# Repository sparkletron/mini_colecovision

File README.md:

# Mini Colecovision Project with Super Game Module Support
### Schematic, PCB, and CPLD design.

---

  author: Jay Convertino

  date: 2024.03.24

  details: A Super Game Module Compatible Colecovision that is much smaller than the original, and only uses +5v.

  license: MIT

---

## LICENSE
  - All files related to or generated from the KiCAD source fall under the MIT license.
  - All files related to or generated from the Verilog source fall under the MIT license.
  - All files generated by me, Jay Convertino, fall under the MIT license.
  - All files from other sources fall under the license of their specification.

## RELEASE VERSIONS
### Current
  - 1.0.1 - Fixed opcode games AY check for super game module.

### Past
  - 1.0.0 - First working version
  - DEV

### MISC
  - std_v1 - A branch that contains the first version with standard colecovision compatibility only.

## Intro
  This is a miniturization of the original colecovision. All logic is simplified to a single CPLD.

## Documentation
  For detailed usage information, please navigate to one of the following sources. They are the same, just in a different format.
  - [mini_colecovision.pdf](docs/manual/mini_colecovision.pdf)
  - [github page](https://sparkletron.github.io/mini_colecovision/)

## SOURCES
### Schematic Check
  - Righteous Tentacle Colecovision : https://github.com/sparkletron/righteous_tentacle_colecovision : Jay Convertino

## SOFTWARE REQUIREMENTS
  - KiCAD v7.X
  - Quartus v13.0.1sp1 web edition
  - Altera USB Blaster

## BUILD TIPS
  This design is made so anyone can build this. Though it will need a board from a PCB manufacture due to the small pitch and
  vias. There are only a few SMD devices, the CPU, a cap, and a few resistors. These are larger to help make soldering easier.

  Recommend populating the SMD parts first, then moving on to the through hole parts from passive to active. If you do not plan
  on using a battery pack the shotkey diodes can be omitted.

  This is a 4 layer board, power and ground planes are run on the two internal planes.

  All case parts are ABS Plastic.

## Completed Project Image

## PCB IMAGE

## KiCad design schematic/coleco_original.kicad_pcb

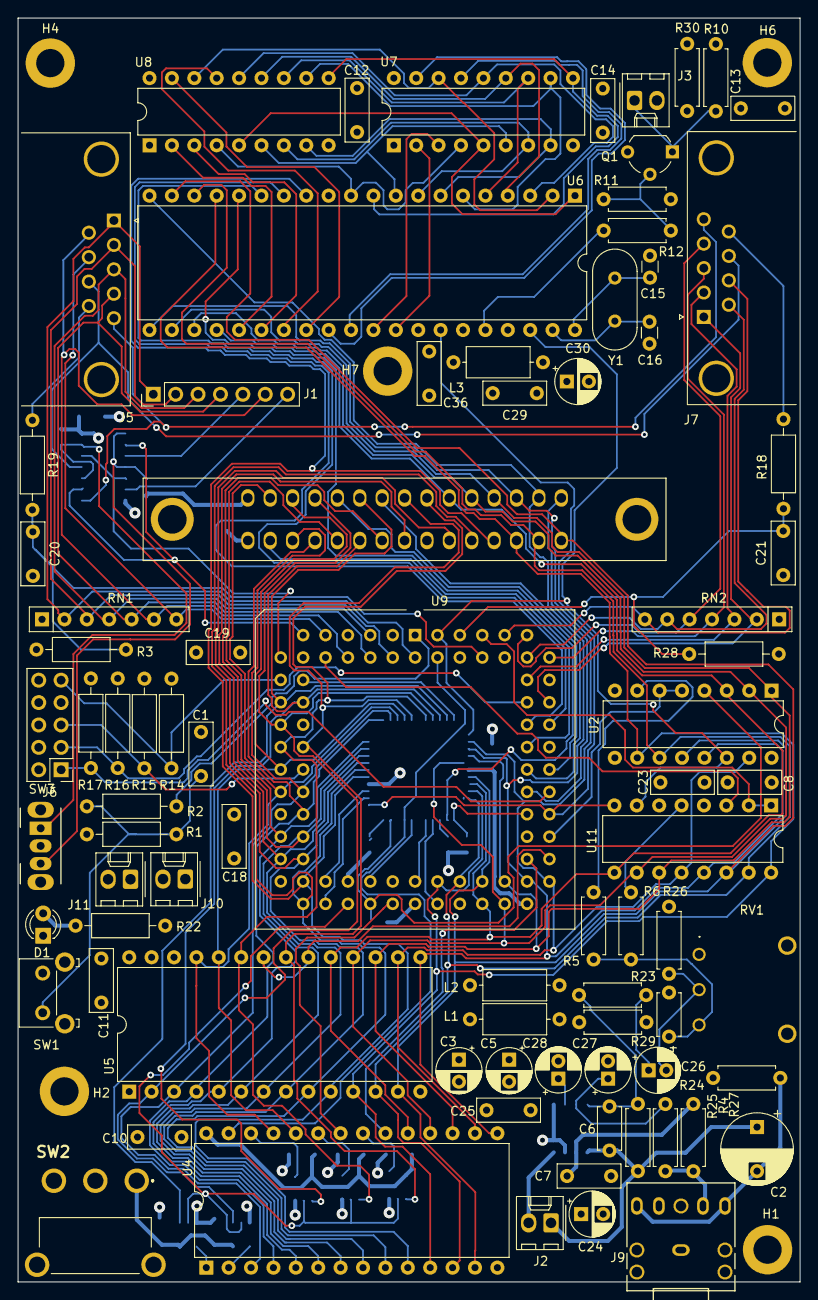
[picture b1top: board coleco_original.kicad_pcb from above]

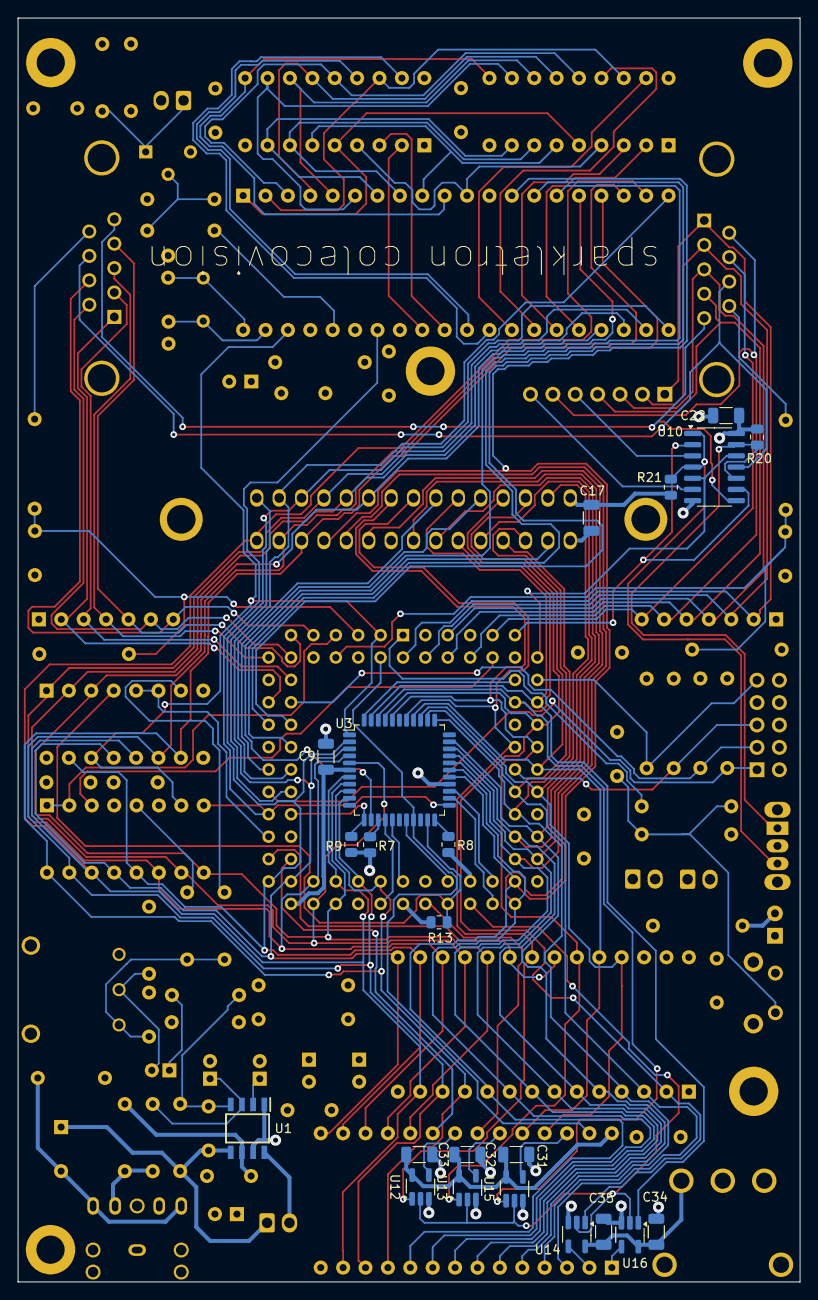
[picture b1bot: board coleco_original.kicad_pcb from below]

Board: 4 copper layers, 88.7 x 143.4 mm, 110 parts (22 on the bottom side), 130 nets.

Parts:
C1, C7, C8, C10, C11, C12, C13, C14, C18, C19, C23, C25, C29, C36: 100nF; C_Disc_D7.0mm_W2.5mm_P5.00mm
C2: 330uF; CP_Radial_D8.0mm_P5.00mm
C3, C5, C24, C30: 10uF; CP_Radial_D5.0mm_P2.50mm
C4: 100pF; C_Disc_D4.7mm_W2.5mm_P5.00mm
C6: 270pF; C_Disc_D4.7mm_W2.5mm_P5.00mm
C9, C17, C22, C31, C32, C33, C34, C35: 100nF; C_1206_3216Metric
C15, C16: 33pF; C_Disc_D3.0mm_W1.6mm_P2.50mm
C20, C21: 10nF; C_Disc_D7.0mm_W2.5mm_P5.00mm
C26: 0.47uF; CP_Radial_D5.0mm_P2.00mm
C27: 0.1uF; CP_Radial_D5.0mm_P2.00mm
C28: 2.2uF; CP_Radial_D5.0mm_P2.00mm
D1: LED; LED_D3.0mm
H1, H2, H4, H6, H7: MountingHole_Pad; MountingHole_3.2mm_M3_DIN965_Pad
J1: Conn_01x07; PinHeader_1x07_P2.54mm_Vertical
J2, J10, J11: Conn_01x02; Molex_KK-254_AE-6410-02A_1x02_P2.54mm_Vertical
J3: Conn_Coaxial; Molex_KK-254_AE-6410-02A_1x02_P2.54mm_Vertical
J4: Cartridge Port; 55308412_coleco
J5: Player 1; DSUB-9_Male_Horizontal_P2.77x2.84mm_EdgePinOffset7.70mm_Hou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
J6: Conn_02x05_Odd_Even; PinHeader_2x05_P2.54mm_Vertical
J7: Player 2; DSUB-9_Male_Horizontal_P2.77x2.84mm_EdgePinOffset7.70mm_Hou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
J9: SJ1-3525NG; SJ1-3525NG_CUD
L1, L2, L3: 4.7uH; L_Axial_L7.0mm_D3.3mm_P10.16mm_Horizontal_Fastron_MICC
Q1: 2N3904; TO-92_Wide
R1: 4k7; R_Axial_DIN0207_L6.3mm_D2.5mm_P10.16mm_Horizontal
R2: 470R; R_Axial_DIN0207_L6.3mm_D2.5mm_P10.16mm_Horizontal
R3, R28: 100k; R_Axial_DIN0207_L6.3mm_D2.5mm_P10.16mm_Horizontal
R4, R27: 100K; R_Axial_DIN0207_L6.3mm_D2.5mm_P7.62mm_Horizontal
R5, R6: 2k2; R_Axial_DIN0207_L6.3mm_D2.5mm_P7.62mm_Horizontal
R7, R8, R9: 3K3; R_0805_2012Metric
R10: 75R; R_Axial_DIN0207_L6.3mm_D2.5mm_P7.62mm_Horizontal
R11: 510R; R_Axial_DIN0207_L6.3mm_D2.5mm_P7.62mm_Horizontal
R12: 100R; R_Axial_DIN0207_L6.3mm_D2.5mm_P7.62mm_Horizontal
R13: 3k3; R_0805_2012Metric
R14, R15, R16, R17: 1k; R_Axial_DIN0207_L6.3mm_D2.5mm_P10.16mm_Horizontal
R18, R19: 10k; R_Axial_DIN0207_L6.3mm_D2.5mm_P10.16mm_Horizontal
R20: 1K; R_0805_2012Metric
R21: 1k; R_0805_2012Metric
R22: 220R; R_Axial_DIN0207_L6.3mm_D2.5mm_P10.16mm_Horizontal
R23: 10K; R_Axial_DIN0207_L6.3mm_D2.5mm_P7.62mm_Horizontal
R24, R26: 1K; R_Axial_DIN0207_L6.3mm_D2.5mm_P7.62mm_Horizontal
R25: 68K; R_Axial_DIN0207_L6.3mm_D2.5mm_P7.62mm_Horizontal
R29, R30: 2R; R_Axial_DIN0207_L6.3mm_D2.5mm_P7.62mm_Horizontal
RN1, RN2: 10k; R_Array_SIP7
RV1: 10K; RV100F304K1B50K
S1: sparkletron
SW1: SW_Push; SW_Tactile_SKHH_Angled
SW2: SW_SPDT; 1101M2S3ABE2
SW3: SW_SPDT; SW_CuK_OS102011MA1QN1_SPDT_Angled
U1: TPA711D; SOIC127P600X175-8N
U2: SN76489AN; DIP-16_W7.62mm
U3: Z84C0010AEG; LQFP-44_10x10mm_P0.8mm
U4: CY62256-55PC; DIP-28_W15.24mm
U5: 27C256; DIP-28_W15.24mm
U6: TMS9118NL; DIP-40_W15.24mm
U7, U8: TMS4416; DIP-18_W7.62mm
U9: EPM7128SLC; PLCC-84_THT-Socket
U10: 74ABT125; SOIC-14_3.9x8.7mm_P1.27mm
U11: YMZ284; DIP-16_W7.62mm
U12, U13, U14, U15, U16: 74AHCT1G08; SOT-23-5_HandSoldering
Y1: 10.738635 MHz; Crystal_HC49-4H_Vertical

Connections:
+5P: C12.1, C14.1, C36.1, L3.1, R30.2, U6.33 (VCC), U7.9 (VDD), U8.9 (VDD)
+5V: C3.1, C9.1, C10.1, C11.1, C17.1, C18.1, C19.1, C22.1, C25.2, C29.1, C30.1, C31.1, C32.1, C33.1, C34.1, C35.1, J4.30, J6.4, J11.1, L1.2, L2.2, L3.2, R1.1, R3.2, R7.2, R8.1, R9.2, R13.2, R14.2, R15.2, R16.2, R20.1, R21.2, R22.1, R28.2, RN1.1 (common), RN2.1 (common), SW2.3 (C), U3.6 (+5V), U4.28 (VCC), U5.1 (VPP), U5.26 (A13), U5.27 (A14), U5.28 (VCC), U9.3 (VCCINT), U9.13 (VCCIO), U9.26 (VCCIO), U9.38 (VCCIO), U9.43 (VCCITN), U9.53 (VCCIO), U9.66 (VCCIO), U9.78 (VCCIO), U10.14 (VCC), U12.5 (VCC), U13.5 (VCC), U14.5 (VCC), U15.5 (VCC), U16.5 (VCC)
+5VA: C7.1, C24.1, R27.2, R29.2, U1.6 (VDD)
+5VD: C5.1, C8.1, C23.1, L2.1, U2.16 (VCC), U11.4 (VDD)
+5VP: C13.1, Q1.3 (C), R30.1
/GLUE/A0: J4.7, U3.27 (A0), U4.10 (A0), U5.10 (A0), U6.13 (MODE), U9.34 (I/O)
/GLUE/A1: J4.9, U3.28 (A1), U4.9 (A1), U5.9 (A1), U9.33 (I/O)
/GLUE/A2: J4.11, U3.29 (A2), U4.8 (A2), U5.8 (A2), U9.31 (I/O)
/GLUE/A3: J4.15, U3.30 (A3), U4.7 (A3), U5.7 (A3), U9.30 (I/O)
/GLUE/A4: J4.17, U3.31 (A4), U4.6 (A4), U5.6 (A4), U9.29 (I/O)
/GLUE/A5: J4.21, U3.32 (A5), U4.5 (A5), U5.5 (A5), U9.28 (I/O)
/GLUE/A6: J4.23, U3.34 (A6), U4.4 (A6), U5.4 (A6), U9.27 (I/O)
/GLUE/A7: J4.25, U3.35 (A7), U4.3 (A7), U5.3 (A7), U9.25 (I/O)
/GLUE/A8: J4.28, U3.36 (A8), U4.25 (A8), U5.25 (A8), U9.24 (I/O)
/GLUE/A9: J4.26, U3.37 (A9), U4.24 (A9), U5.24 (A9), U9.22 (I/O)
/GLUE/A10: J4.16, U3.38 (A10), U5.21 (A10), U9.21 (I/O), U12.1
/GLUE/A11: J4.14, U3.40 (A11), U5.23 (A11), U9.20 (I/O), U13.1
/GLUE/A12: J4.24, U3.41 (A12), U5.2 (A12), U9.18 (I/O), U14.1
/GLUE/A13: J4.19, U3.42 (A13), U9.17 (I/O), U15.1
/GLUE/A14: J4.20, U3.43 (A14), U9.16 (I/O), U16.1
/GLUE/A15: U3.44 (A15), U9.15 (I/O)
/GLUE/AS: U9.10 (I/O), U11.3 (A0)
/GLUE/C1P1: J1.1, J5.1, RN1.2 (R1), U9.2 (INPUT/OE2/(GCLK2))
/GLUE/C1P2: J1.2, J5.2, RN1.3 (R2), U9.4 (I/O)
/GLUE/C1P3: J1.3, J5.3, RN1.4 (R3), U9.5 (I/O)
/GLUE/C1P4: J1.4, J5.4, RN1.5 (R4), U9.6 (I/O)
/GLUE/C1P6: J1.6, J5.6, RN1.6 (R5), U9.8 (I/O)
/GLUE/C1P7: J5.7, RN1.7 (R6), U9.9 (I/O)
/GLUE/C1P9: C20.1, R3.1, R19.2, U9.80 (I/O)
/GLUE/C2P1: J7.1, RN2.2 (R1), U9.70 (I/O)
/GLUE/C2P2: J7.2, RN2.3 (R2), U9.73 (I/O)
/GLUE/C2P3: J7.3, RN2.4 (R3), U9.74 (I/O)
/GLUE/C2P4: J7.4, RN2.5 (R4), U9.75 (I/O)
/GLUE/C2P6: J7.6, RN2.6 (R5), U9.76 (I/O)
/GLUE/C2P7: J7.7, RN2.7 (R6), U9.77 (I/O)
/GLUE/C2P9: C21.1, R18.2, R28.1, U9.81 (I/O)
/GLUE/C5_ARM: U9.11 (I/O), U10.2, U10.9
/GLUE/C8_FIRE: U9.12 (I/O), U10.5, U10.12
/GLUE/CLK: U2.14 (CLK), U3.1 (CLK), U6.38 (CPUCLK), U9.83 (INPUT/GCLK1), U11.7 (CLK)
/GLUE/D0: J4.5, U2.10 (D7), U3.9 (D0), U4.11 (Q0), U5.11 (D0), U6.17 (CD7), U9.46 (I/O), U11.16 (D0)
/GLUE/D1: J4.3, U2.11 (D6), U3.10 (D1), U4.12 (Q1), U5.12 (D1), U6.18 (CD6), U9.48 (I/O), U11.15 (D1)
/GLUE/D2: J4.1, U2.12 (D5), U3.7 (D2), U4.13 (Q2), U5.13 (D2), U6.19 (CD5), U9.50 (I/O), U11.14 (D2)
/GLUE/D3: J4.4, U2.13 (D4), U3.3 (D3), U4.15 (Q3), U5.15 (D3), U6.20 (CD4), U9.55 (I/O), U11.13 (D3)
/GLUE/D4: J4.6, U2.15 (D3), U3.2 (D4), U4.16 (Q4), U5.16 (D4), U6.21 (CD3), U9.54 (I/O), U11.12 (D4)
/GLUE/D5: J4.8, U2.1 (D2), U3.4 (D5), U4.17 (Q5), U5.17 (D5), U6.22 (CD2), U9.52 (I/O), U11.11 (D5)
/GLUE/D6: J4.10, U2.2 (D1), U3.5 (D6), U4.18 (Q6), U5.18 (D6), U6.23 (CD1), U9.51 (I/O), U11.10 (D6)
/GLUE/D7: J4.12, U2.3 (D0), U3.8 (D7), U4.19 (Q7), U5.19 (D7), U6.24 (CD0), U9.49 (I/O), U11.9 (D7)
/GLUE/TCK: J6.1, R17.1, U9.62 (I/O/(TCK))
/GLUE/TDI: J6.9, R14.1, U9.14 (I/O/(TDI))
/GLUE/TDO: J6.3, R16.1, U9.71 (I/O/(TDO))
/GLUE/TMS: J6.5, R15.1, U9.23 (I/O/(TMS))
/GLUE/~AY_SND_ENABLE: U9.79 (I/O), U11.1 (~WR), U11.2 (~CS)
/GLUE/~CSR: U6.15 (~CSR), U9.68 (I/O)
/GLUE/~CSW: U6.14 (~CSW), U9.69 (I/O)
/GLUE/~CS_h8000: J4.18, U9.65 (I/O)
/GLUE/~CS_hA000: J4.22, U9.64 (I/O)
/GLUE/~CS_hC000: J4.2, U9.63 (I/O)
/GLUE/~CS_hE000: J4.27, U9.67 (I/O)
/GLUE/~INT: R9.1, U3.12 (~INT), U9.61 (I/O)
/GLUE/~IORQ: U3.16 (~IORQ), U9.44 (I/O)
/GLUE/~M1: U3.24 (~M1), U9.35 (I/O)
/GLUE/~MREQ: U3.15 (~MREQ), U9.45 (I/O)
/GLUE/~RAM_CS: U4.20 (~CS), U9.57 (I/O)
/GLUE/~RAM_OE: U4.22 (~OE), U9.41 (I/O)
/GLUE/~RD: U3.18 (~RD), U9.40 (I/O)
/GLUE/~RESET_SW: R2.2, U9.1 (INPUT/GLCRn)
/GLUE/~RESET: U3.23 (~RESET), U6.34 (~RESET), U9.60 (I/O), U11.8 (~RESET)
/GLUE/~RFSH: U3.25 (~RFSH), U9.36 (I/O)
/GLUE/~ROM_ENABLE: U5.20 (~CE), U5.22 (~OE), U9.56 (I/O)
/GLUE/~SND_ENABLE: U2.5 (~WE), U2.6 (~CE), U9.58 (I/O)
/GLUE/~WAIT: R13.1, U2.4 (RDY), U3.21 (~WAIT), U9.39 (I/O)
/GLUE/~WR: U3.19 (~WR), U4.27 (~WE), U9.84 (INPUT/OE1)
/controller/ex_ARM: J5.5, J7.5, U10.8
/controller/ex_FIRE: J5.8, J7.8, U10.11
/controller/ex_disable: R20.2, SW3.1 (A), U10.10, U10.13
/controller/in_ARM: J1.5, U10.3
/controller/in_FIRE: J1.7, U10.6
/controller/in_disable: R21.1, SW3.3 (C), U10.1, U10.4
/cpu/~BUSRQ: R8.2, U3.22 (~BUSREQ)
/cpu/~HALT: R7.1, U3.14 (~HALT)
/cpu/~NMI: U3.13 (~NMI), U6.16 (~INT)
/sound/HP+: C2.2, J9.2, J9.3, R24.2
/sound/HP_BTL: J9.4, R4.1, R27.1
/sound/SP+: C2.1, C6.1, J2.1, R25.2, U1.5 (VO+)
/sound/SP-: J2.2, U1.8 (VO-)
/storage/A10e: U4.21 (A10), U12.4
/storage/A11e: U4.23 (A11), U13.4
/storage/A12e: U4.2 (A12), U14.4
/storage/A13e: U4.26 (A13), U15.4
/storage/A14e: U4.1 (A14), U16.4
/storage/ram_mirror: U9.37 (I/O), U12.2, U13.2, U14.2, U15.2, U16.2
/video/AD0: U6.10 (AD0), U7.10 (A7), U8.10 (A7)
/video/AD1: U6.9 (AD1), U7.6 (A6), U8.6 (A6)
/video/AD2: U6.8 (AD2), U7.7 (A5), U8.7 (A5)
/video/AD3: U6.7 (AD3), U7.8 (A4), U8.8 (A4)
/video/AD4: U6.6 (AD4), U7.11 (A3), U8.11 (A3)
/video/AD5: U6.5 (AD5), U7.12 (A2), U8.12 (A2)
/video/AD6: U6.4 (AD6), U7.13 (A1), U8.13 (A1)
/video/AD7: U6.3 (AD7), U7.14 (A0), U8.14 (A0)
/video/R0: U6.32 (RD0), U7.2 (DQ1)
/video/R1: U6.31 (RD1), U7.3 (DQ2)
/video/R2: U6.30 (RD2), U7.15 (DQ3)
/video/R3: U6.29 (RD3), U7.17 (DQ4)
/video/R4: U6.28 (RD4), U8.17 (DQ4)
/video/R5: U6.27 (RD5), U8.15 (DQ3)
/video/R6: U6.26 (RD6), U8.3 (DQ2)
/video/R7: U6.25 (RD7), U8.2 (DQ1)
/video/RnW: U6.11 (R/~W), U7.4 (~W), U8.4 (~W)
/video/Y: R12.2, U6.36 (COMVID)
/video/nCAS: U6.2 (~CAS), U7.16 (~CAS), U8.16 (~CAS)
/video/nRAS: U6.1 (~RAS), U7.5 (~RAS), U8.5 (~RAS)
GNDD: C1.2, C3.2, C4.1, C5.2, C7.2, C8.2, C9.2, C10.2, C11.2, C12.2, C13.2, C14.2, C15.1, C16.2, C17.2, C18.2, C19.2, C20.2, C21.2, C22.2, C23.2, C24.2, C25.1, C27.2, C28.2, C29.2, C30.2, C31.2, C32.2, C33.2, C34.2, C35.2, C36.2, D1.1 (K), J3.2 (Ext), J4.29, J6.2, J6.10, J9.1, J10.2, J11.2, R10.1, R11.2, R17.2, R24.1, R26.1, RV1.1, SW1.2, SW3.2 (B), U1.1 (SHUTDOWN), U1.7 (GND), U2.8 (GND), U3.26 (GND), U4.14 (GND), U5.14 (GND), U6.12 (VSS), U7.1 (~G), U7.18 (VSS), U8.1 (~G), U8.18 (VSS), U9.7 (GND), U9.19 (GND), U9.32 (GND), U9.42 (GND), U9.47 (GND), U9.59 (GND), U9.72 (GND), U9.82 (GND), U10.7 (GND), U11.6 (GND), U12.3 (GND), U13.3 (GND), U14.3 (GND), U15.3 (GND), U16.3 (GND)
unnamed: C1.1, R1.2, R2.1, SW1.1
unnamed: C4.2, R5.1, R6.1, RV1.3
unnamed: C26.1, R23.1
unnamed: C26.2, R26.2, RV1.2
unnamed: D1.2 (A), R22.2
unnamed: J3.1 (In), Q1.1 (E), R10.2
unnamed: J5.9, R19.1
unnamed: J7.9, R18.1
unnamed: J10.1, SW2.2 (B)
unnamed: L1.1, R29.1
unnamed: Q1.2 (B), R11.1, R12.1
unnamed: C28.1, U1.2 (BYPASS)
unnamed: C6.2, R23.2, R25.1, U1.4 (IN)
unnamed: C27.1, R4.2, U1.3 (SE/~BTL)
unnamed: R5.2, U2.7 (OUT)
unnamed: C15.2, U6.40 (XTAL1), Y1.1
unnamed: C16.1, U6.39 (XTAL2), Y1.2
unnamed: R6.2, U11.5 (OUT)

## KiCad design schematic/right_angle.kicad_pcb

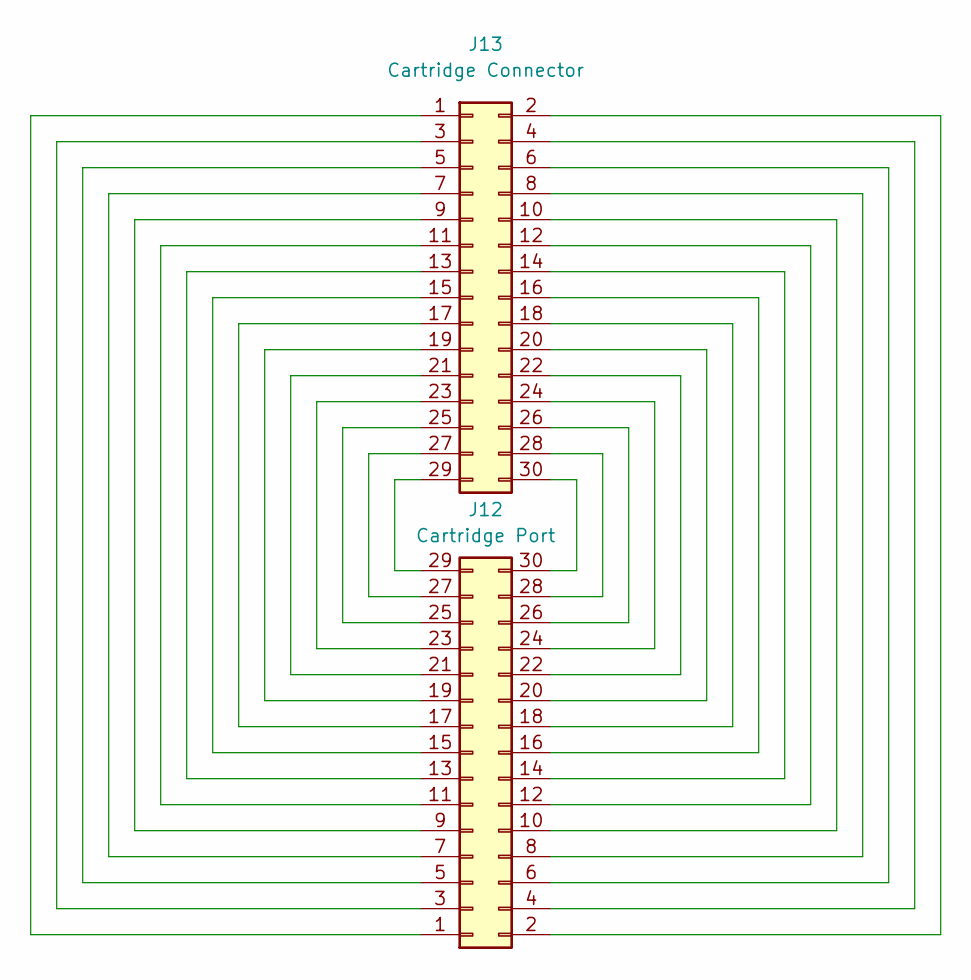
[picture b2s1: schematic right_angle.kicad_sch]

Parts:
J12: Cartridge Port; 55308412_coleco
J13: Cartridge Connector; Colecovision_Cartridge

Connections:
unnamed: J12.1, J13.1
unnamed: J12.2, J13.2
unnamed: J12.3, J13.3
unnamed: J12.4, J13.4
unnamed: J12.5, J13.5
unnamed: J12.6, J13.6
unnamed: J12.7, J13.7
unnamed: J12.8, J13.8
unnamed: J12.9, J13.9
unnamed: J12.10, J13.10
unnamed: J12.11, J13.11
unnamed: J12.12, J13.12
unnamed: J12.13, J13.13
unnamed: J12.14, J13.14
unnamed: J12.15, J13.15
unnamed: J12.16, J13.16
unnamed: J12.17, J13.17
unnamed: J12.18, J13.18
unnamed: J12.19, J13.19
unnamed: J12.20, J13.20
unnamed: J12.21, J13.21
unnamed: J12.22, J13.22
unnamed: J12.23, J13.23
unnamed: J12.24, J13.24
unnamed: J12.25, J13.25
unnamed: J12.26, J13.26
unnamed: J12.27, J13.27
unnamed: J12.28, J13.28
unnamed: J12.29, J13.29
unnamed: J12.30, J13.30

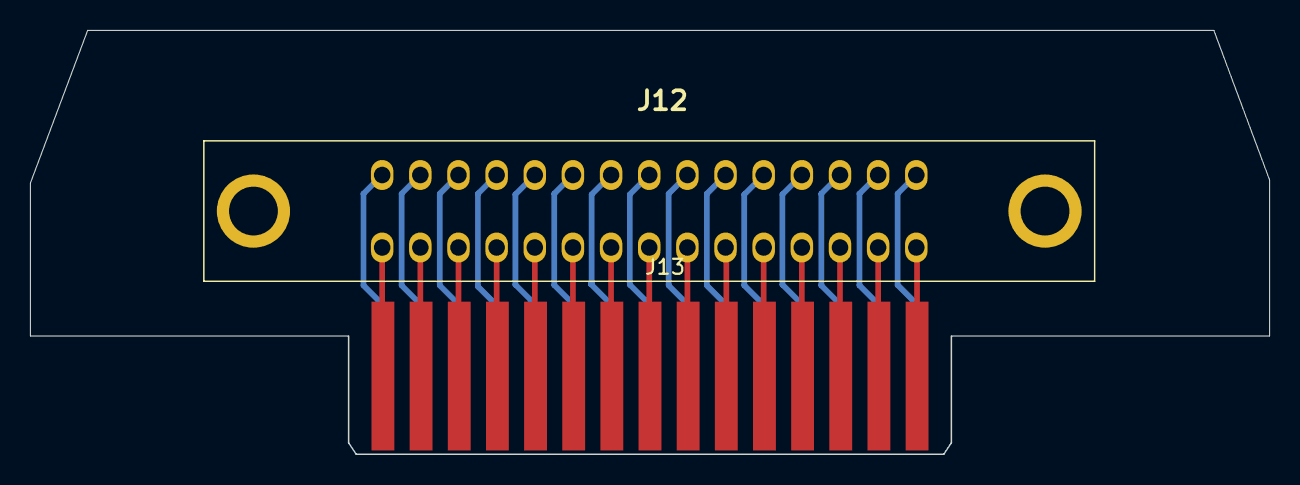
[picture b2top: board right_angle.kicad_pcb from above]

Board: 2 copper layers, 82.5 x 28.2 mm, 3 parts (0 on the bottom side), 30 nets.

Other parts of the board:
S1: sparkletron

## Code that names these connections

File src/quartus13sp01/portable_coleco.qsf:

# -------------------------------------------------------------------------- #
#
# Copyright (C) 1991-2013 Altera Corporation
# Your use of Altera Corporation's design tools, logic functions
# and other software and tools, and its AMPP partner logic
# functions, and any output files from any of the foregoing
# (including device programming or simulation files), and any
# associated documentation or information are expressly subject
# to the terms and conditions of the Altera Program License
# Subscription Agreement, Altera MegaCore Function License
# Agreement, or other applicable license agreement, including,
# without limitation, that your use is for the sole purpose of
# programming logic devices manufactured by Altera and sold by
# Altera or its authorized distributors.  Please refer to the
# applicable agreement for further details.
#
# -------------------------------------------------------------------------- #
#
# Quartus II 64-Bit
# Version 13.0.1 Build 232 06/12/2013 Service Pack 1 SJ Web Edition
# Date created = 17:47:30  December 31, 2023
#
# -------------------------------------------------------------------------- #
#
# Notes:
#
# 1) The default values for assignments are stored in the file:
#		portable_coleco_assignment_defaults.qdf
#    If this file doesn't exist, see file:
#		assignment_defaults.qdf
#
# 2) Altera recommends that you do not modify this file. This
#    file is updated automatically by the Quartus II software
#    and any changes you make may be lost or overwritten.
#
# -------------------------------------------------------------------------- #


set_global_assignment -name FAMILY MAX7000S
set_global_assignment -name DEVICE "EPM7128SLC84-10"
set_global_assignment -name TOP_LEVEL_ENTITY porta_glue_coleco
set_global_assignment -name ORIGINAL_QUARTUS_VERSION "13.0 SP1"
set_global_assignment -name PROJECT_CREATION_TIME_DATE "17:47:30  DECEMBER 31, 2023"
set_global_assignment -name LAST_QUARTUS_VERSION "13.0 SP1"
set_global_assignment -name PROJECT_OUTPUT_DIRECTORY output_files
set_global_assignment -name ERROR_CHECK_FREQUENCY_DIVISOR "-1"
set_global_assignment -name EDA_SIMULATION_TOOL "ModelSim-Altera (Verilog)"
set_global_assignment -name EDA_OUTPUT_DATA_FORMAT "VERILOG HDL" -section_id eda_simulation
set_global_assignment -name OPTIMIZE_HOLD_TIMING OFF
set_global_assignment -name OPTIMIZE_MULTI_CORNER_TIMING OFF
set_global_assignment -name FITTER_EFFORT "STANDARD FIT"
set_global_assignment -name MAX7000_DEVICE_IO_STANDARD TTL
set_global_assignment -name SDC_FILE ../portable_coleco/constr/porta_glue_coleco.sdc
set_global_assignment -name VERILOG_FILE ../portable_coleco/src/porta_glue_coleco.v
set_location_assignment PIN_15 -to A[15]
set_location_assignment PIN_16 -to A[14]
set_location_assignment PIN_17 -to A[13]
set_location_assignment PIN_18 -to A[12]
set_location_assignment PIN_20 -to A[11]
set_location_assignment PIN_21 -to A[10]
set_location_assignment PIN_22 -to A[9]
set_location_assignment PIN_24 -to A[8]
set_location_assignment PIN_25 -to A[7]
set_location_assignment PIN_27 -to A[6]
set_location_assignment PIN_28 -to A[5]
set_location_assignment PIN_29 -to A[4]
set_location_assignment PIN_30 -to A[3]
set_location_assignment PIN_31 -to A[2]
set_location_assignment PIN_33 -to A[1]
set_location_assignment PIN_34 -to A[0]
set_location_assignment PIN_2  -to C1P1
set_location_assignment PIN_4  -to C1P2
set_location_assignment PIN_5  -to C1P3
set_location_assignment PIN_6  -to C1P4
set_location_assignment PIN_8  -to C1P6
set_location_assignment PIN_9  -to C1P7
set_location_assignment PIN_80 -to C1P9
set_location_assignment PIN_70 -to C2P1
set_location_assignment PIN_73 -to C2P2
set_location_assignment PIN_74 -to C2P3
set_location_assignment PIN_75 -to C2P4
set_location_assignment PIN_76 -to C2P6
set_location_assignment PIN_77 -to C2P7
set_location_assignment PIN_81 -to C2P9
set_location_assignment PIN_68 -to CSRn
set_location_assignment PIN_69 -to CSWn
set_location_assignment PIN_65 -to CS_h8000n
set_location_assignment PIN_64 -to CS_hA000n
set_location_assignment PIN_63 -to CS_hC000n
set_location_assignment PIN_67 -to CS_hE000n
set_location_assignment PIN_49 -to D[7]
set_location_assignment PIN_51 -to D[6]
set_location_assignment PIN_52 -to D[5]
set_location_assignment PIN_54 -to D[4]
set_location_assignment PIN_55 -to D[3]
set_location_assignment PIN_50 -to D[2]
set_location_assignment PIN_48 -to D[1]
set_location_assignment PIN_46 -to D[0]
set_location_assignment PIN_44 -to IORQn
set_location_assignment PIN_35 -to M1n
set_location_assignment PIN_45 -to MREQn
set_location_assignment PIN_57 -to RAM_CSn
set_location_assignment PIN_37 -to RAM_MIRROR
set_location_assignment PIN_1  -to RESETn_SW
set_location_assignment PIN_36 -to RFSHn
set_location_assignment PIN_56 -to ROM_ENABLEn
set_location_assignment PIN_58 -to SND_ENABLEn
set_location_assignment PIN_61 -to INTn
set_location_assignment PIN_39 -to WAITn
set_location_assignment PIN_84 -to WRn
set_location_assignment PIN_83 -to clk
set_location_assignment PIN_60 -to RESETn
set_location_assignment PIN_41 -to RAM_OEn
set_location_assignment PIN_40 -to RDn
set_location_assignment PIN_11 -to CP5_ARM
set_location_assignment PIN_12 -to CP8_FIRE
set_location_assignment PIN_79 -to AY_SND_ENABLEn
set_location_assignment PIN_10 -to AS

set_global_assignment -name SLOW_SLEW_RATE ON

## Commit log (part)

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2022-11-03 init commit
2022-11-03 fix ascii
2022-11-03 spelling
2022-11-08 reorganized repo
2022-12-28 added hi-res pics of stripped PCB
2022-12-28 first day of pcb trace, working pin by of the z80 cpu. Last pin completed: 7
2022-12-29 revised schematic into sheets for easier design. Looks much better.
2022-12-30 changed all vintage library names to better represent future ideas. Removed parts not needed... for now. Updated schmematic symbols.
2022-12-31 Up to pin 29 on z80 done. Address 0 to 10 left. Only tracing to its end point for the most part. Each chip gets traced chip to chip in this manned
2022-12-31 completed Z80 trace of PCB. off to a good start.
2023-01-02 added rf modulation schematic, added dram to vdp. Fixed +5vc to +5v
2023-01-02 added u6 decoder lines, renamed a few lines to make sense to there destination.
2023-01-03 completed sound block, finished cart io port, and finished decoder.
2023-01-03 fixed some more line names, added a expansion port io pin.
2023-01-03 started work on clock_reset_misc circuits. inverter u7 done, u8 added and starting work around U22.
2023-01-04 first version of clock-reset circuits. Its a bit complicated and will need some revisions.
2023-01-04 altered and did some cleanup of the way the wires were run. Finished expansion port routes to rf modulator. Added ext_psu for future external power supply design (will be an off the shelf psu block).
2023-01-04 RF modulator completed, rough draft complete. Next step is to clean-up all pages.
2023-01-08 Cleanup clock-reset-invert schematic. Checked against wiki.console5.com/wiki/Colecovision. Had a inverter backwards (after cleanup it was obvious since its a standard circuit). Everything else checks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
2023-01-08 cleanup on the controller schematic. Checked against wiki.console5.com/wiki/Colecovision. Found a mistake with INT line thanks to the wiki. R21/R22 is reversed between the schematics. Aka R21 is plac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
2023-01-08 cleaup of rf circuits. much better flow vs the original. Comparing to the wiki.console5.com/wiki/Colecovision shows many differences. Not sure I agree with it at all. Going to use the ADAM schematic 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
2023-01-09 cleaned up RF circuit again, and used ChildOfCv schematic as a ref. Fixed a few mistakes. I didn't know his even existed. Its a very nice project. I didn't know it existed till I was googling some so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
2023-01-09 added my refs so people will know where the 2nd phase of checks came from. its really helped the effort, the goal is to reverse the board from the original, and use online sources to check, and then 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
2023-01-10 all lines renamed, based most of the names from the coleco adam schematic. CS cart lines are my own, and the rest are from the wiki schematic for the controller... those will need to be checked.
2023-01-15 cleanup, and started associating components
2023-01-16 added new libs for rest of the parts. some still need updating for correct parts, but for now they work. PCB import complete.
2023-01-16 created edge cut outline for coleco pcb. updated expansion connector edge cut to be the correct size (using a 0.8 mm cutting end in my mill).
2023-02-06 first draft of board with components added, no traces
2023-02-07 added a quick version of the RF board. Not checked at all.
2023-02-12 fixed RF board placement, not perfect, but needs to align to new component sizes
2023-02-13 RF on main board components setup correctly.
2023-02-20 added controller traces and some around it.
2023-02-20 added addr decode and 4066 circuit
2023-02-20 added video memory connections
2023-02-28 fixed a bug on the +5v line, added +5NF (no filter) net list names. Added traces to the ram, and inverter, and select ics.
2023-03-02 added memory, eprom and sound lines. some video as well. fixed the cap size for polar. its a bit weird since they use 5 mm pin and 5mm body and bend out the leads.
2023-03-04 updated license and added info to readme
2023-03-04 working on eeprom, cart port, cpu
2023-03-05 first rough draft completed. very rough, needs alot of cleanup. all rats connected besides board to board.
2023-03-05 compress images to fit on github
2023-03-05 changed files again since PNG was the issue
2023-03-11 working on top layer, improved the routing and respacing traces.
2023-03-13 added a new jack with matching pin names. started fixing drc errors. start working on power trace sizes.
2023-03-14 added new models, fixed the drc errors. changed power width.
2023-03-14 change connector to female
2023-03-14 added power cable pinout, cleanup finished on main page of schematic, now fits US letter page.
2023-03-17 added pads for switch and RF shield, RF shield still needs adjustment
2023-03-17 fixed mount spacing, added labels, and added new version of reset switch.
2023-03-19 cleanup controller schematic
2023-03-19 cleanup main schematic to remove crossing lines
2023-03-19 added pdf schematic, cleanup pdf files, added 3D image, updated readme
2023-03-23 fixed cart for 12 mil isolation routing. Now minimum trace isolation is 12 mil. Trace width min is 12 mil. This is easier to build.
2023-03-23 tweak rf schematic
2023-03-24 trace cleanup, and RF mod schematic cleanup
2023-03-24 more trace cleanup
2023-03-25 adjusted connector and switch to remove ignored clearance errors
2023-03-25 adjust gnd iso width to better connect all grounds in video ram (20 down to 12mil)
2023-03-25 added pics to repo, removed main_board project
2023-03-28 changed via size to 22 mill for better fitment
2023-03-29 cleanup and readjust of traces, copied to gerber export projects.
2023-03-30 enlarged mount holes to match coleco, adjusted placement of two. adjusted traces for new holes.
2023-04-03 fixed two resistors that were the wrong value wrong, 270. correct 120.
2023-04-03 changed the board from the original so the control ports can be soldered from the bottom. standard dsub 9 bin connectors don't work on non-plated hole designs. All other parts can be soldered top and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
2023-04-03 adjusted controller ports again, now they are totally soldered from the bottom for front and BACK rows. added some no fill zones and some general cleanup as well.
2023-04-03 added mounting holes, future proof the video section for jumper selection of voltages between 4516/4116 chips
2023-04-04 adjusted rf mod porition for better flow
2023-04-06 moved crystal line to bottom for easier soldering.
2023-04-07 changed crystal a bit more to make double sided non-plated through hole designs easier. This time top traces rerouted to avoid shorts from the crystal body.
2023-04-08 updated docs/datasheets with all of the ICS. updated readme to help people better navigate the repo.
2023-04-08 github links suck
2023-04-08 fixed indent on file list
2023-04-09 fixed value of resistors on RF board, fixed placement of resistors on RF board
2023-04-09 fixed readme indents
2023-04-10 adjusting RF layout, seems to have issues with the previous layout with noise
2023-04-11 fixed footprint lead size
2023-04-13 changed switch to one that is a better match for the old (larger)
2023-04-14 update routing of rf board to fix loop over pin
2023-05-01 changed a few traces, and updated a few parts. cleanup to make building easier so resistors don't have vias under them for npth builds
2023-05-01 cleanup for release of version 1
2023-05-05 added first set of digital signal captures
2023-05-05 made sure all schematic parts are up to date
2023-05-10 updated switch to fix isolation size. fixed some traces to prevent shorts when being build at home with mills or etching methods.
2023-05-13 updated gerbers and main/rf exports
2023-05-21 fixed pad size for switch
2023-05-22 fixed 5v via so it doesn't hold up the resistor
2023-05-23 adjusted 5 volt trace on 7405
2023-05-23 fixed the switch for the sub-rf board to match the original coleco for chan 3/4 selection
2023-05-25 first commit of verison 1.0.0, missing documents for signals and 3D enclosure.
2023-05-26 whoops, spelling for the win
2023-05-26 added info to pic names
2023-05-26 added vdp pics
2023-05-26 ntsc note
2023-05-26 updated readme defines for folders
2023-05-26 added intro
2023-05-26 added image
2023-05-26 update to kicad 7.0, ipt stuff added
2023-05-28 added new power supply info
2023-05-28 added 3D printed case parts... in progress.
2023-05-28 added new kicad 3d model of pcb... coleco_original3.iam is the best. odd bug that the switch comes out clear
2023-05-28 updated kicad pcb hole to be only 10 mils to the right. That seemed to work perfect, and the new printed shell fits the board decently enough.
2023-06-19 3D printed part adjust, fix cart position.
2023-06-19 added F to revision, update date
2023-06-20 added images of case, updated readme.
2023-12-27 inital change to cpld
2024-01-04 first commit of portable coleco, major changes... pcb meh. CPLD code tested, quartus build works.
2024-01-06 first prototype board complete with smd ram
2024-01-07 First version sent out for build. 6116 as a DIP makes the design easier.
2024-01-07 changed traces to 8 mil, 8 mil iso. allows for better routing of lines that didn't need to be as thick as they were.
2024-01-08 moved JTAG connector over to make room for power on side of board
2024-02-03 stash
2024-02-03 bootup works, controller waits, but no response
2024-02-03 update sdc settings
2024-02-03 added volume and adjusted cart port
2024-02-03 improve nand circuit for controller enable, since clocked version works fine, just use and xor to indicated its time to flip flop enables
2024-02-04 first iteration of version v1. PCB placed, checked but needs final go through and case design before send out.
2024-03-24 first version with roller controller compat
2024-03-24 update gitignore and add images
2024-03-24 cleanup quartus
2024-03-24 update images in readme
2024-03-24 wrong image extension
2024-03-24 added board images, old version, missing holes and C*P9 resistors and caps.
2024-03-24 add output files for all CPLD targets
2024-03-25 remove lock files
2024-03-25 fix ref for schematic, add bin folder
2024-03-25 update license file so github will use it
2024-04-20 updated output jacks to correct footprint
2024-04-20 added logic to CPLD for super game module. Shadow registers for ymz284 can not be complete due to size. Hopefully the last write will do.
2024-04-20 tweaks to routing to help make better grounds
2024-04-21 code cleanup and fix sound cache out tristate vector
2024-05-01 added 3D models
2024-07-13 fix registers so they are set at reset
2024-07-13 change audio port so it does not conflict with volume knob
2024-08-02 working on new 4 layer version. This is intender to improve the ground connections in hopes of better audio output. Added inductors for pi filters going to digital sound chips and analog audio amp.
2024-08-03 added filtering to the video circuit. Idea is to to keep the video and audio circuits as clean and seperated as possible for the power rails.
2024-08-10 revised controller select circuit
2024-10-03 update cpld to 7128 in schematic
2024-10-05 update for release, correct documents, and update readme
2024-10-05 add case images
2024-10-16 complete ram mirror when banks not enabled.
2024-11-07 schematic updates to remove unused video port
2024-11-07 added banner to readme
2024-11-07 testing name change by hand
2024-11-07 png image test
2024-11-07 change jpg to png
2024-11-07 update html and pdf link
2024-11-07 looks to be a cache issue in edge, go figure
2024-11-08 added rough draft of documentation
2024-11-08 forgot to change path
2024-11-08 documentation updates
2024-11-08 update verilog comment to P2
2024-11-08 correct error in fusesoc section
2024-11-08 move pdf schematic to make a bit more sense
2024-11-11 move sub schematics to folders. add usb_to_roller psu, untested
2024-11-23 move controller
2024-11-23 remove unneeded stuffs
2025-02-10 roller controller
2025-02-17 cleanup document manual to include better bom. Remove and document other files
2025-02-28 stl models added
2025-02-28 update manual with 3d printed bare bones
